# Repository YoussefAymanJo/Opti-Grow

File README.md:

# Opti-Grow

## Description 
Optic-grow is an closed-loop feedback system.A system that monitors and act based on lavendar & lettuce coditions in Wadi el natroun , Egypt.It handle plants temperature , Humidty & soil moisture and lighht intesity,preserving plant between optiman conditions high and low point.As it use actuctors,peltiers,humidifier , heatinglamp ,grow ligth ,  water pump and fan.It powered by esp s3.and cloud base storage of firebase,show data at moment on web app.

## Why it was built
It is about the challenge Egypt faces in intergrating IOT closed Systems with farming.Our Project solve this by providing high nutrition needed crop in Wadi el notroun all the year.Lavendar & lettuce controlled by feedback system.that control temperature & Humidty & soil moisture & light intensity parameter.

## How to use it / Build it
Firstly,Buying all electronics parts,then buy and cuts wood into blocks ,by using CNC machine for actuators.After that,assemble all together using nails and wood glue.hen adding electronic compontes sesnor & actucators.and connect them first to power supply to test it.then connect each one alone first to esp ,then test them all.after that,check wire isolation and system working and real data from sesnors.test system manul for 2 h. Finally, add plants and soil.

## Schematic 

We  made symbols & footprints for missing parts in kicad,then wires them ,and add pin headers instead of wire sensor direct to pcb,finally,organize schematic and adding flow diagram of system feedback.

## PCB 
pcb consist of pinheaders and will connect to sensors using isolated wires & jumpers,and actuctors will connect to relayes .we made pcb on kicad,body outline first,the routed componets together.

## CAD
we assembled greenhouse on fusion and make enclosure for pcb ,power supply & buck. 

## Firmware 
I made esp code and web to monitor data form firebase,but i will add js part later during building

### WEB

### ESP 

## BOM

 we made the BOM and needed materials ,in egypt then convert its price to USD dollar.

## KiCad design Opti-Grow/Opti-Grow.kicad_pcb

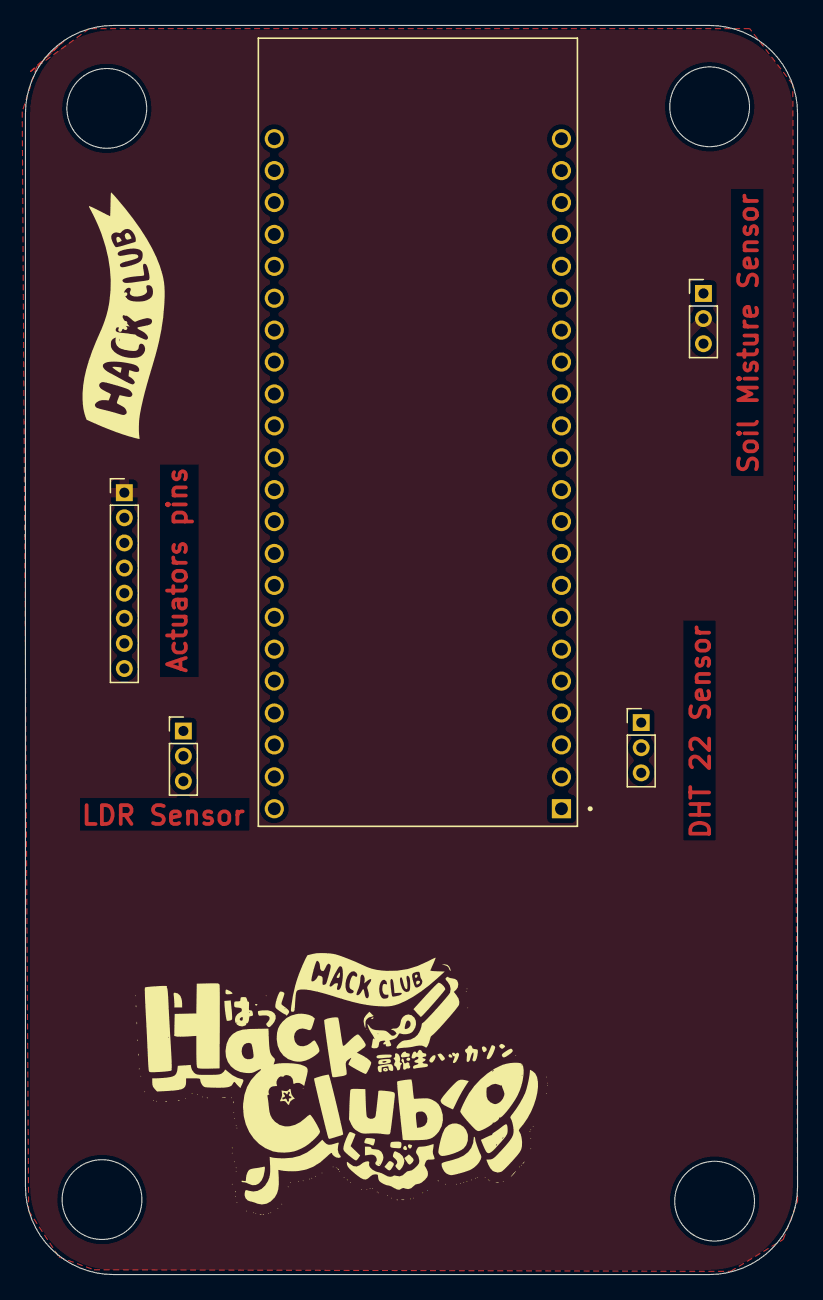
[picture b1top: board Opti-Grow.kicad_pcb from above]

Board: 2 copper layers, 61.5 x 99.4 mm, 4 parts (0 on the bottom side), 3 nets, no tracks yet.

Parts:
J1: Soil Moisture Sensor; PinHeader_1x03_P2.00mm_Vertical
J3: DHT22 Sensor; PinHeader_1x03_P2.00mm_Vertical
J4: LDR Sensor; PinHeader_1x03_P2.00mm_Vertical
J5: Actuators pins; PinHeader_1x08_P2.00mm_Vertical

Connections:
GND: J1.1, J3.1, J4.2, J5.2
VCC: J1.2, J5.1
VCC 3V: J3.3, J4.3
